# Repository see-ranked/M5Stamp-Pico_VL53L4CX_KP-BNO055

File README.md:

# M5Stamp Pico + VL53L4CX + KP-BNO055 KiCad Project

このプロジェクトは、M5Stamp-Pico、ToF距離センサ「VL53L4CX」、9軸センサモジュール「KP-BNO055」で構成された回路設計のKiCadプロジェクトです。

## プロジェクト構成

```
m5stamp-pico_VL53L4CX_KP-BNO055/
├── Circuit/              # KiCad回路設計ファイル
│   ├── Circuit.kicad_pro # プロジェクトファイル
│   ├── Circuit.kicad_sch # 回路図ファイル
│   ├── Circuit.kicad_pcb # PCBレイアウトファイル
│   ├── Circuit.kicad_dru # デザインルールファイル（JLCPCB用）
│   ├── sym-lib-table     # シンボルライブラリテーブル
│   └── fp-lib-table      # フットプリントライブラリテーブル
└── Library/              # カスタムライブラリ
    ├── M5Stamp-Pico-Board/
    ├── KP-BNO055/
    ├── A295-CTRPB-1/     # USB Type-Cコネクタ
    ├── TCA9548A/         # I2Cマルチプレクサ
    └── SS12D00G3/        # スライドスイッチ
```

## 使用コンポーネント

- **M5Stamp-Pico**: ESP32-PICO-D4搭載の小型開発ボード
- **VL53L4CX**: STMicroelectronics製ToF距離センサ
- **KP-BNO055**: Bosch製9軸センサモジュール（加速度・ジャイロ・地磁気）
- **TCA9548A**: I2Cマルチプレクサ（複数のI2Cデバイス管理用）
- **A295-CTRPB-1**: USB Type-Cコネクタ（秋月電子通商）
- **SS12D00G3**: スライドスイッチ

## 必要なソフトウェア

- **KiCad 9.0以降**: [https://www.kicad.org/](https://www.kicad.org/)

## 回路図の確認方法

1. **KiCadを起動**
   - KiCadを開きます

2. **プロジェクトを開く**
   - `File` → `Open Project...` を選択
   - `Circuit/Circuit.kicad_pro` を開きます

3. **回路図エディタを開く**
   - プロジェクトマネージャーで `Circuit.kicad_sch` をダブルクリック
   - または、`Schematic Editor` アイコンをクリック

4. **回路図を確認**
   - マウスホイールでズーム
   - マウス中ボタンドラッグでパン（移動）
   - 各コンポーネントの接続を確認できます

5. **電気ルールチェック（ERC）の実行**（オプション）
   - `Inspect` → `Electrical Rules Checker...` を選択
   - `Run ERC` をクリックして回路のエラーをチェック

## PCBレイアウトの確認方法

1. **PCBエディタを開く**
   - プロジェクトマネージャーで `Circuit.kicad_pcb` をダブルクリック
   - または、`PCB Editor` アイコンをクリック

2. **PCBレイアウトを確認**
   - マウスホイールでズーム
   - マウス中ボタンドラッグでパン（移動）
   - 基板の外形、部品配置、配線を確認できます

3. **3Dビューアで確認**（オプション）
   - `View` → `3D Viewer` を選択
   - 基板の3Dモデルを確認できます
   - マウスドラッグで回転、ホイールでズーム

4. **デザインルールチェック（DRC）の実行**（オプション）
   - `Inspect` → `Design Rules Checker...` を選択
   - `Run DRC` をクリックして製造可能性をチェック
   - JLCPCB用のデザインルール（`Circuit.kicad_dru`）が適用されています

## JLCPCBへの発注手順

### 1. ガーバーファイルの生成

1. **PCBエディタを開く**
   - `Circuit.kicad_pcb` を開きます

2. **ガーバーファイルを出力**
   - `File` → `Fabrication Outputs` → `Gerbers (.gbr)...` を選択
   - 出力先ディレクトリを指定（例: `Circuit/gerber/`）
   - 以下のレイヤーが選択されていることを確認:
     - `F.Cu` (表面銅箔)
     - `B.Cu` (裏面銅箔)
     - `F.Paste` (表面ペースト)
     - `B.Paste` (裏面ペースト)
     - `F.Silkscreen` (表面シルク)
     - `B.Silkscreen` (裏面シルク)
     - `F.Mask` (表面レジスト)
     - `B.Mask` (裏面レジスト)
     - `Edge.Cuts` (基板外形)
   - `Plot` をクリック

3. **ドリルファイルを出力**
   - 同じダイアログで `Generate Drill Files...` をクリック
   - `Drill File Format`: `Excellon` を選択
   - `Map File Format`: `Gerber` を選択（オプション）
   - `Generate Drill File` をクリック
   - ダイアログを閉じる

### 2. ガーバーファイルのZIP圧縮

1. **ガーバーファイルをまとめる**
   - 生成されたすべての `.gbr` ファイルと `.drl` ファイルを選択
   - ZIPファイルに圧縮（例: `Circuit_gerber.zip`）

### 3. JLCPCBでの発注

1. **JLCPCBサイトにアクセス**
   - [https://jlcpcb.com/](https://jlcpcb.com/) を開く

2. **ガーバーファイルをアップロード**
   - `Order Now` または `Quote Now` をクリック
   - `Add gerber file` ボタンをクリック
   - 作成したZIPファイルをアップロード

3. **基板仕様を確認・設定**
   - アップロード後、自動的に基板サイズが検出されます
   - 以下の項目を確認・設定:
     - **PCB Qty**: 基板枚数（最小5枚）
     - **Layers**: 2層
     - **PCB Thickness**: 1.6mm（標準）
     - **PCB Color**: お好みの色（緑が最安）
     - **Surface Finish**: HASL（標準）または ENIG（推奨）
     - **Copper Weight**: 1oz
     - **Remove Order Number**: Yes（基板に注文番号を印字しない場合）

4. **SMT実装サービス（オプション）**
   - 部品実装を依頼する場合:
     - `SMT Assembly` を `Yes` に設定
     - BOMファイルとCPLファイル（部品配置ファイル）が必要
     - ※このプロジェクトではBOM/CPLファイルは含まれていません

5. **カートに追加**
   - 仕様を確認後、`Save to Cart` をクリック

6. **チェックアウト**
   - カートを確認し、`Secure Checkout` をクリック
   - 配送先住所、配送方法、支払い方法を入力
   - 注文を確定

### 4. 製造・配送

- **製造期間**: 通常2-3営業日
- **配送期間**: 配送方法により異なる（DHL: 3-5日、OCS: 7-15日など）
- **追跡**: 注文後、追跡番号がメールで送られます

## デザインルールについて

このプロジェクトには、JLCPCB 2層基板用のデザインルール（`Circuit.kicad_dru`）が含まれています。

- **最小トレース幅**: 0.127mm (5mil)
- **最小クリアランス**: 0.127mm (5mil)
- **最小ビア径**: 0.3mm（ドリル径: 0.2mm）

これらのルールはJLCPCBの標準仕様に準拠しています。

## ライブラリについて

`Library/` ディレクトリには、このプロジェクトで使用するカスタムコンポーネントのKiCadライブラリが含まれています。各ライブラリには個別のREADMEファイルがあり、詳細な情報が記載されています。

- **M5Stamp-Pico-Board**: M5Stamp Pico用のシンボルとフットプリント
- **KP-BNO055**: 9軸センサモジュール用のライブラリ
- **A295-CTRPB-1**: USB Type-Cコネクタ（秋月電子通商）
- **TCA9548A**: I2Cマルチプレクサ用のライブラリ
- **SS12D00G3**: スライドスイッチ用のライブラリ

## トラブルシューティング

### ライブラリが見つからない

- `sym-lib-table` と `fp-lib-table` が正しく設定されているか確認
- ライブラリパスが `${KIPRJMOD}/../Library/` を使用して相対パスで指定されているか確認

### DRCエラーが出る

- JLCPCB用のデザインルール（`Circuit.kicad_dru`）が読み込まれているか確認
- `File` → `Board Setup` → `Design Rules` で設定を確認

### ガーバーファイルが正しく生成されない

- すべての必要なレイヤーが選択されているか確認
- ドリルファイル（`.drl`）も生成されているか確認

## ライセンス

このプロジェクトのライセンスについては、プロジェクトオーナーにお問い合わせください。

## 貢献

バグ報告や改善提案は、GitHubのIssuesでお願いします。

---

**注意**: このREADMEは、KiCad 9.0を基準に作成されています。他のバージョンでは手順が異なる場合があります。

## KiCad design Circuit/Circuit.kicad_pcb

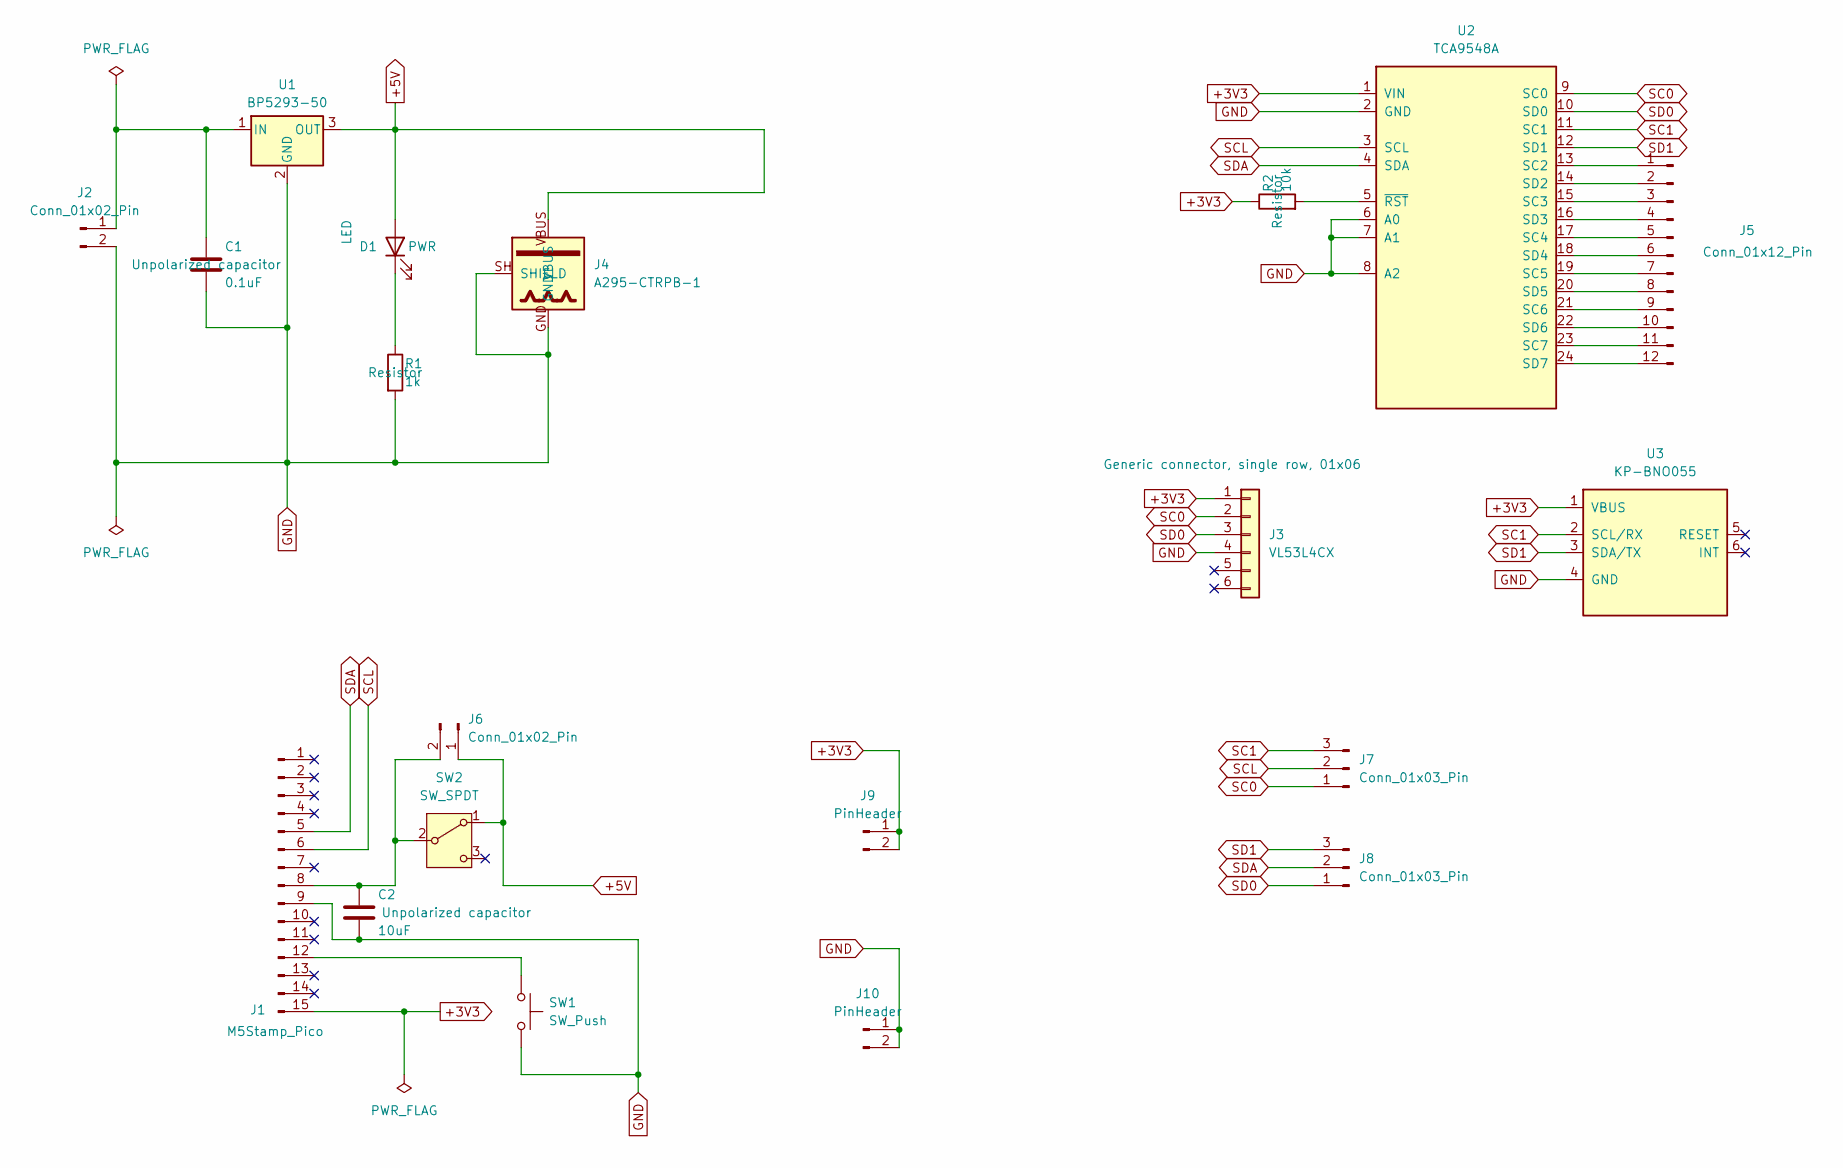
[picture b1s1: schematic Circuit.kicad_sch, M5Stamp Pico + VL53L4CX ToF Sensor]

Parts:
C1: 0.1uF; C_Disc_D3.0mm_W1.6mm_P2.50mm
C2: 10uF; C_Radial_D5.0mm_H5.0mm_P2.00mm
D1: PWR; LED_D5.0mm
J1: M5Stamp_Pico; M5Stamp-Pico-Board
J2, J6: Conn_01x02_Pin; PinHeader_1x02_P2.54mm_Vertical
J3: VL53L4CX; PinHeader_1x06_P2.54mm_Vertical
J4: A295-CTRPB-1; MPN A295-CTRPB-1
J5: Conn_01x12_Pin; PinHeader_1x12_P2.54mm_Vertical
J7, J8: Conn_01x03_Pin; PinHeader_1x03_P2.54mm_Vertical
J9, J10: PinHeader; PinHeader_1x02_P2.54mm_Vertical
R1: 1k; R_Axial_DIN0207_L6.3mm_D2.5mm_P10.16mm_Horizontal
R2: 10k; R_Axial_DIN0207_L6.3mm_D2.5mm_P10.16mm_Horizontal
SW1: SW_Push; SW_PUSH_6mm
SW2: SW_SPDT; SS12D00G3
U1: BP5293-50; TO-220-3_Horizontal_TabDown
U2: TCA9548A; TCA9548A_Breakout
U3: KP-BNO055

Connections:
+3V3: J1.15, J3.1, J9.1, J9.2, R2.1, U2.1 (VIN), U3.1 (VBUS)
+5V: D1.2 (A), J4.VBUS, J6.1, SW2.1 (A), U1.3 (OUT)
GND: C1.2, C2.2, J1.9, J2.2, J3.4, J4.GND, J4.SH (SHIELD), J10.1, J10.2, R1.2, SW1.2, U1.2 (GND), U2.2 (GND), U2.6 (A0), U2.7 (A1), U2.8 (A2), U3.4 (GND)
unnamed: D1.1 (K), R1.1
unnamed: C2.1, J1.8, J6.2, SW2.2 (B)
unnamed: J1.12, SW1.1
unnamed: C1.1, J2.1, U1.1 (IN)
unnamed: J5.1, U2.13 (SC2)
unnamed: J5.2, U2.14 (SD2)
unnamed: J5.3, U2.15 (SC3)
unnamed: J5.4, U2.16 (SD3)
unnamed: J5.5, U2.17 (SC4)
unnamed: J5.6, U2.18 (SD4)
unnamed: J5.7, U2.19 (SC5)
unnamed: J5.8, U2.20 (SD5)
unnamed: J5.9, U2.21 (SC6)
unnamed: J5.10, U2.22 (SD6)
unnamed: J5.11, U2.23 (SC7)
unnamed: J5.12, U2.24 (SD7)
unnamed: R2.2, U2.5 (~RST)
SC0: J3.2, J7.1, U2.9 (SC0)
SC1: J7.3, U2.11 (SC1), U3.2 (SCL/RX)
SCL: J1.6, J7.2, U2.3 (SCL)
SD0: J3.3, J8.1, U2.10 (SD0)
SD1: J8.3, U2.12 (SD1), U3.3 (SDA/TX)
SDA: J1.5, J8.2, U2.4 (SDA)

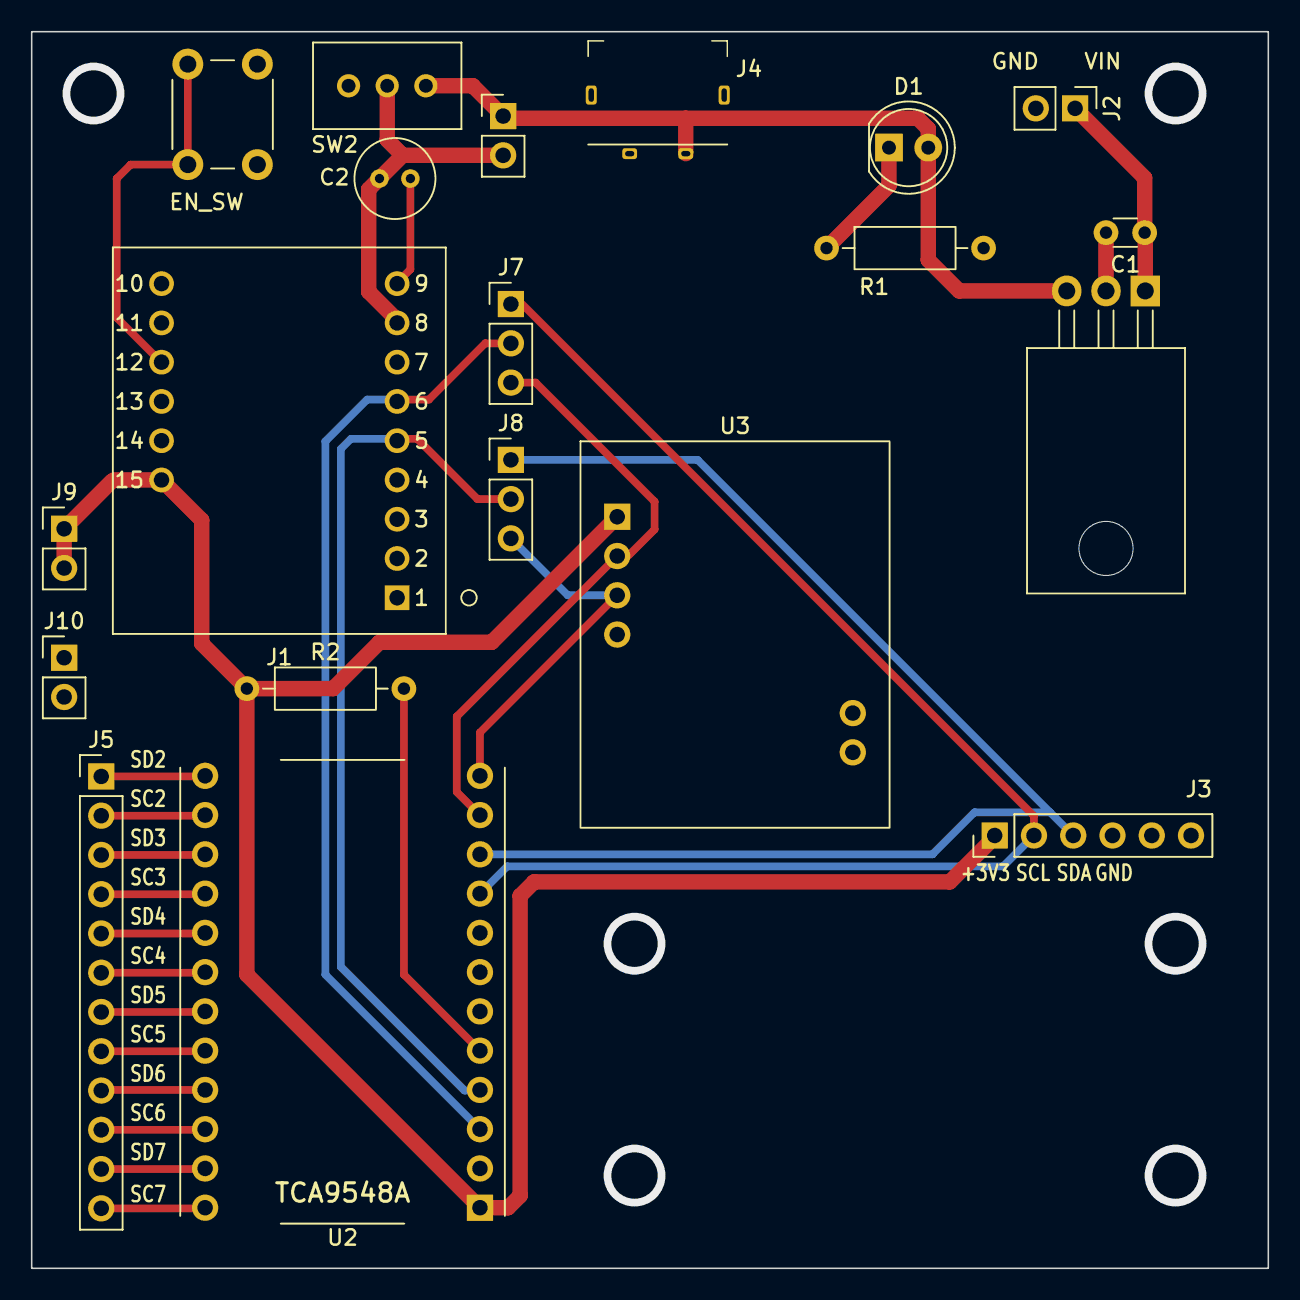
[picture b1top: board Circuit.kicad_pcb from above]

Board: 2 copper layers, 80.0 x 80.0 mm, 20 parts (0 on the bottom side), 26 nets.

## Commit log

2026-01-19 Uploading the first version
2026-01-20 Add files via upload
    Upload new component
2026-01-20 Delete Library/PinHeaders_for_M5Stamp_Pico directory
    Deleted the old one due to name change
2026-01-20 Add files via upload
    Upload the README for this project
2026-01-25 Update M5Stamp-Pico-Board.kicad_mod
    The spacing between the left and right pin rows has been increased by 2.54 mm.
2026-01-25 Update to support M5stamp footprint correction
